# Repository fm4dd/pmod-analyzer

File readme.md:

## PMOD Analyzer

### Description

The PMOD Analyzer implements a twin-connector, pass-through PMOD board that routes 2x8 I/O signals from pinheader to pinsocket with breakout into a 18-pin 2.54mm header row for connecting protocol analyzers, and 20 test points for mini-grabber hook-ups that are useful for oscilloscope measurements. Lastly, each signal can be individually switched on to drive a control LED on each I/O line. This makes it ideal for troubleshooting by inserting it between a controller board and PMOD peripherals. With the LEDs switched on, the PMOD can operate "standalone" as a normal LED output board.

http://fpga.fm4dd.com/

### Schematic

### PCB Gerber

| Version | Gerber | Schema |
|---------|--------|--------|
| 1.0     |[20230218-pmod-analyzer-gerber.zip](fabfiles/v10/20230218-pmod-analyzer-gerber.zip) | [20230218-pmod-analyzer-schema.pdf](fabfiles/v10/20230218-pmod-analyzer-schema.pdf) |

### Board Pictures

PMOD Analyzer, connected to the Gatemate E1 FPGA board.

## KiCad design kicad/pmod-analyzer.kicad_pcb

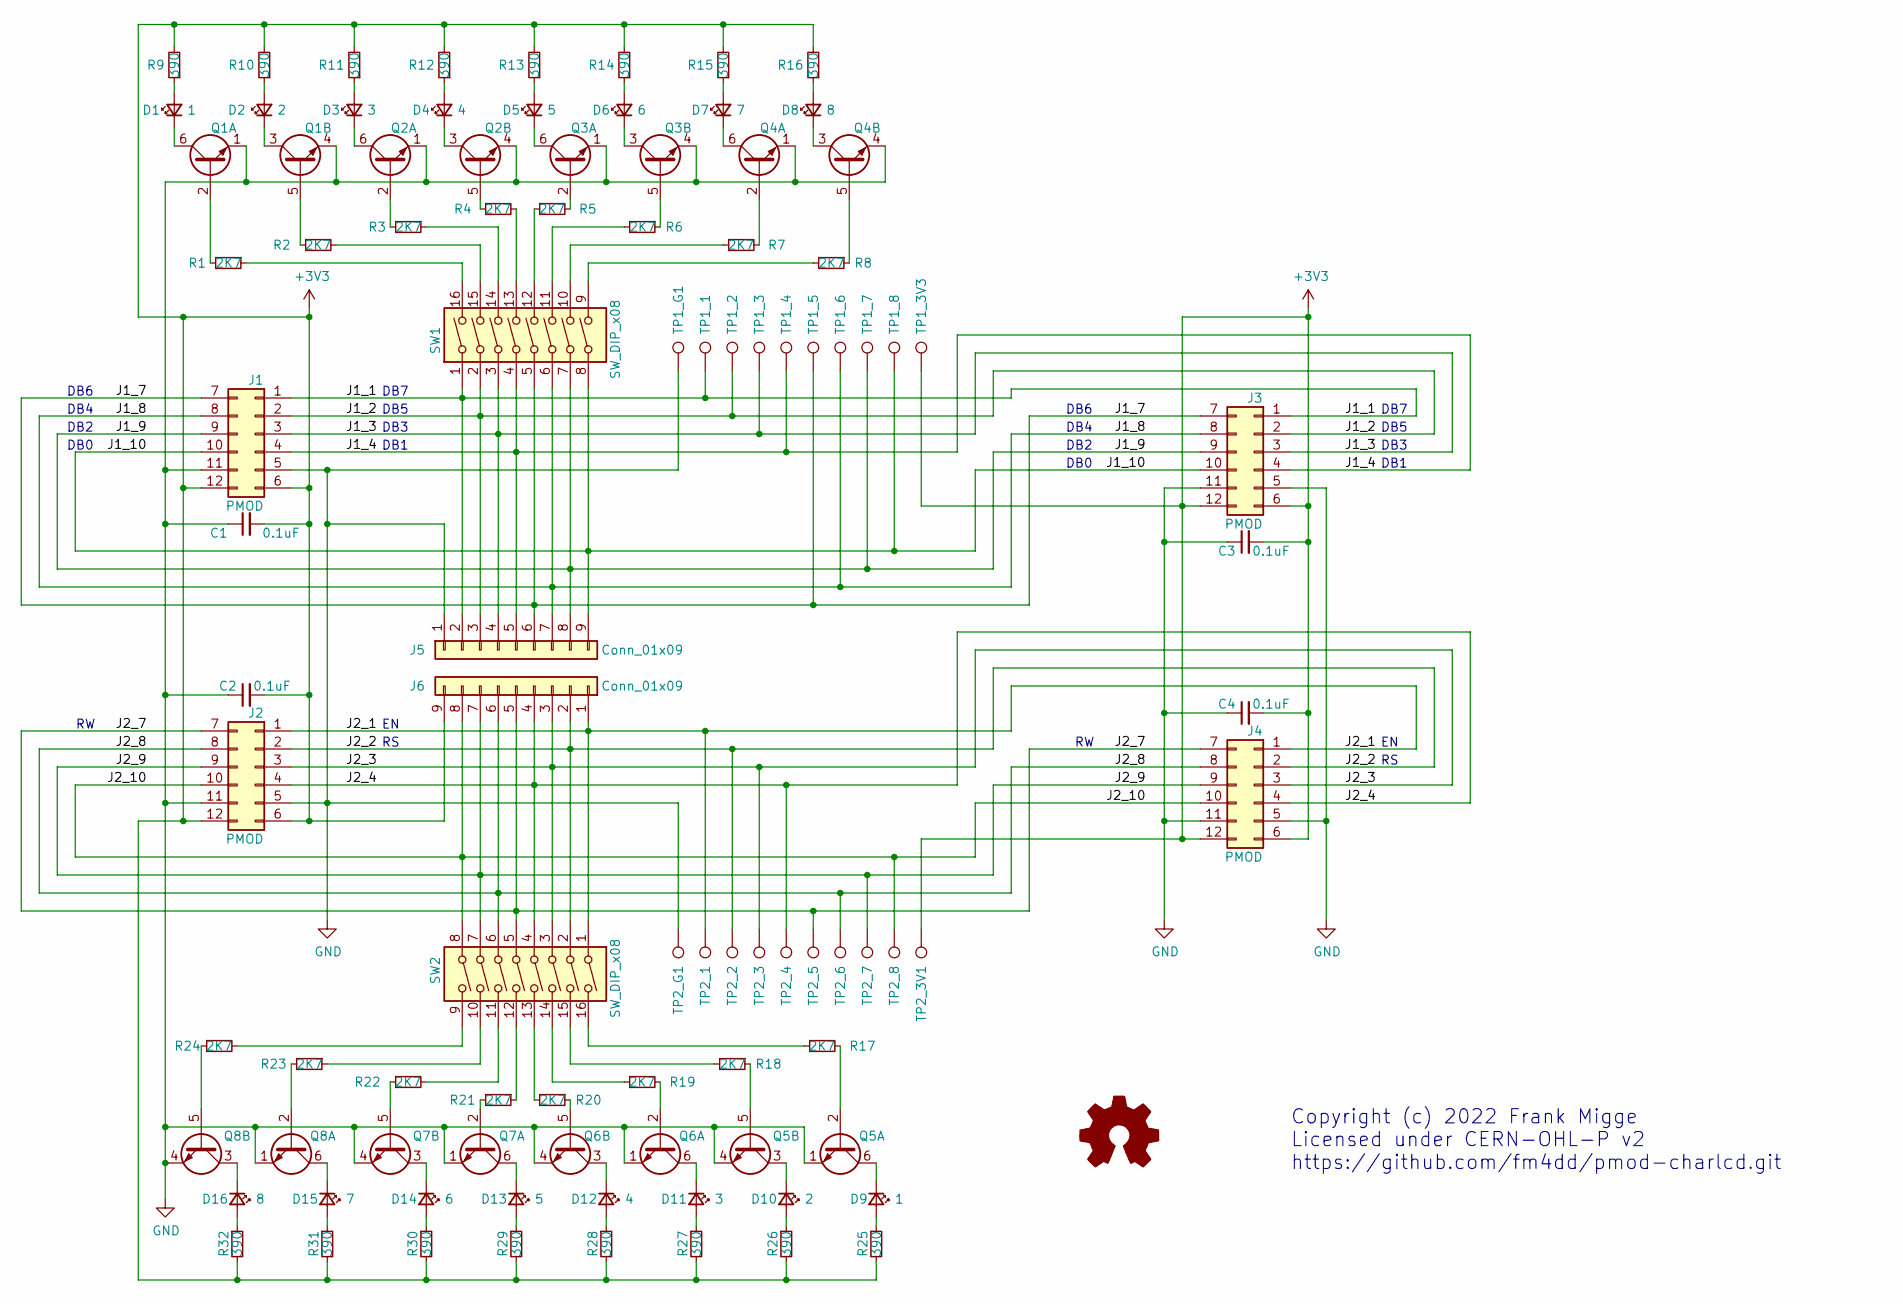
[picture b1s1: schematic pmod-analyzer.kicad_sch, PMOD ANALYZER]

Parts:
C1, C2, C3, C4: 0.1uF; C_0402_1005Metric
D1, D9: 1; LED_0402_FPGA
D2, D10: 2; LED_0402_FPGA
D3, D11: 3; LED_0402_FPGA
D4, D12: 4; LED_0402_FPGA
D5, D13: 5; LED_0402_FPGA
D6, D14: 6; LED_0402_FPGA
D7, D15: 7; LED_0402_FPGA
D8, D16: 8; LED_0402_FPGA
J1, J2: PMOD; PMODHeader_2x06_P2.54mm_Horizontal
J3, J4: PMOD; PMODPinSocket_2x06_P2.54mm_Horizontal
J5, J6: Conn_01x09; PinHeader_1x09_P2.54mm_Vertical
Q1, Q2, Q3, Q4, Q5, Q6, Q7, Q8: Q_Dual_NPN_NPN_E1B1C2E2B2C1; SOT-363_SC-70-6
R1, R2, R3, R4, R5, R6, R7, R8, R17, R18, R19, R20, R21, R22, R23, R24: 2K7; R_0402_1005Metric
R9, R10, R11, R12, R13, R14, R15, R16, R25, R26, R27, R28, R29, R30, R31, R32: 390; R_0402_1005Metric
SW1, SW2: SW_DIP_x08; SW_DIP_SPSTx08_Slide_6.7x21.88mm_W7.62mm_P2.54mm_LowProfile
TP1_1: 1_1; TestPoint_Keystone_5000-5004_Miniature
TP1_2: 1_2; TestPoint_Keystone_5000-5004_Miniature
TP1_3: 1_3; TestPoint_Keystone_5000-5004_Miniature
TP1_3V3: 1_3V; TestPoint_Keystone_5000-5004_Miniature
TP1_4: 1_4; TestPoint_Keystone_5000-5004_Miniature
TP1_5: 1_5; TestPoint_Keystone_5000-5004_Miniature
TP1_6: 1_6; TestPoint_Keystone_5000-5004_Miniature
TP1_7: 1_7; TestPoint_Keystone_5000-5004_Miniature
TP1_8: 1_8; TestPoint_Keystone_5000-5004_Miniature
TP1_G1: 1_G; TestPoint_Keystone_5000-5004_Miniature
TP2_1: 2_1; TestPoint_Keystone_5000-5004_Miniature
TP2_2: 2_2; TestPoint_Keystone_5000-5004_Miniature
TP2_3: 2_3; TestPoint_Keystone_5000-5004_Miniature
TP2_3V1: 2_3V; TestPoint_Keystone_5000-5004_Miniature
TP2_4: 2_4; TestPoint_Keystone_5000-5004_Miniature
TP2_5: 2_5; TestPoint_Keystone_5000-5004_Miniature
TP2_6: 2_6; TestPoint_Keystone_5000-5004_Miniature
TP2_7: 2_7; TestPoint_Keystone_5000-5004_Miniature
TP2_8: 2_8; TestPoint_Keystone_5000-5004_Miniature
TP2_G1: 2_G; TestPoint_Keystone_5000-5004_Miniature

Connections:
+3V3: C1.2, C2.2, C3.2, C4.2, J1.6, J1.12, J2.6, J2.12, J3.6, J3.12, J4.6, J4.12, J6.9, R9.2, R10.2, R11.2, R12.2, R13.2, R14.2, R15.2, R16.2, R25.2, R26.2, R27.2, R28.2, R29.2, R30.2, R31.2, R32.2, TP1_3V3.1, TP2_3V1.1
/J1_1: J1.1, J3.1, J5.2, SW1.1, TP1_1.1
/J1_2: J1.2, J3.2, J5.3, SW1.2, TP1_2.1
/J1_3: J1.3, J3.3, J5.4, SW1.3, TP1_3.1
/J1_4: J1.4, J3.4, J5.5, SW1.4, TP1_4.1
/J1_7: J1.7, J3.7, J5.6, SW1.5, TP1_5.1
/J1_8: J1.8, J3.8, J5.7, SW1.6, TP1_6.1
/J1_9: J1.9, J3.9, J5.8, SW1.7, TP1_7.1
/J1_10: J1.10, J3.10, J5.9, SW1.8, TP1_8.1
/J2_1: J2.1, J4.1, J6.1, SW2.1, TP2_1.1
/J2_2: J2.2, J4.2, J6.2, SW2.2, TP2_2.1
/J2_3: J2.3, J4.3, J6.3, SW2.3, TP2_3.1
/J2_4: J2.4, J4.4, J6.4, SW2.4, TP2_4.1
/J2_7: J2.7, J4.7, J6.5, SW2.5, TP2_5.1
/J2_8: J2.8, J4.8, J6.6, SW2.6, TP2_6.1
/J2_9: J2.9, J4.9, J6.7, SW2.7, TP2_7.1
/J2_10: J2.10, J4.10, J6.8, SW2.8, TP2_8.1
GND: C1.1, C2.1, C3.1, C4.1, J1.5, J1.11, J2.5, J2.11, J3.5, J3.11, J4.5, J4.11, J5.1, Q1.1 (E1), Q1.4 (E2), Q2.1 (E1), Q2.4 (E2), Q3.1 (E1), Q3.4 (E2), Q4.1 (E1), Q4.4 (E2), Q5.1 (E1), Q5.4 (E2), Q6.1 (E1), Q6.4 (E2), Q7.1 (E1), Q7.4 (E2), Q8.1 (E1), Q8.4 (E2), TP1_G1.1, TP2_G1.1
unnamed: D1.2 (A), R9.1
unnamed: D1.1 (K), Q1.6 (C1)
unnamed: D2.2 (A), R10.1
unnamed: D2.1 (K), Q1.3 (C2)
unnamed: D3.2 (A), R11.1
unnamed: D3.1 (K), Q2.6 (C1)
unnamed: D4.2 (A), R12.1
unnamed: D4.1 (K), Q2.3 (C2)
unnamed: D5.2 (A), R13.1
unnamed: D5.1 (K), Q3.6 (C1)
unnamed: D6.2 (A), R14.1
unnamed: D6.1 (K), Q3.3 (C2)
unnamed: D7.2 (A), R15.1
unnamed: D7.1 (K), Q4.6 (C1)
unnamed: D8.2 (A), R16.1
unnamed: D8.1 (K), Q4.3 (C2)
unnamed: D9.2 (A), R25.1
unnamed: D9.1 (K), Q5.6 (C1)
unnamed: D10.2 (A), R26.1
unnamed: D10.1 (K), Q5.3 (C2)
unnamed: D11.2 (A), R27.1
unnamed: D11.1 (K), Q6.6 (C1)
unnamed: D12.2 (A), R28.1
unnamed: D12.1 (K), Q6.3 (C2)
unnamed: D13.2 (A), R29.1
unnamed: D13.1 (K), Q7.6 (C1)
unnamed: D14.2 (A), R30.1
unnamed: D14.1 (K), Q7.3 (C2)
unnamed: D15.2 (A), R31.1
unnamed: D15.1 (K), Q8.6 (C1)
unnamed: D16.2 (A), R32.1
unnamed: D16.1 (K), Q8.3 (C2)
unnamed: Q1.2 (B1), R1.2
unnamed: Q1.5 (B2), R2.1
unnamed: Q2.2 (B1), R3.2
unnamed: Q2.5 (B2), R4.1
unnamed: Q3.2 (B1), R5.2
unnamed: Q3.5 (B2), R6.1
unnamed: Q4.2 (B1), R7.2
unnamed: Q4.5 (B2), R8.1
unnamed: Q5.2 (B1), R17.2
unnamed: Q5.5 (B2), R18.1
unnamed: Q6.2 (B1), R19.2
unnamed: Q6.5 (B2), R20.1
unnamed: Q7.2 (B1), R21.2
unnamed: Q7.5 (B2), R22.1
unnamed: Q8.2 (B1), R23.2
unnamed: Q8.5 (B2), R24.1
unnamed: R1.1, SW1.16
unnamed: R2.2, SW1.15
unnamed: R3.1, SW1.14
unnamed: R4.2, SW1.13
unnamed: R5.1, SW1.12
unnamed: R6.2, SW1.11
unnamed: R7.1, SW1.10
unnamed: R8.2, SW1.9
unnamed: R17.1, SW2.16
unnamed: R18.2, SW2.15
unnamed: R19.1, SW2.14
unnamed: R20.2, SW2.13
unnamed: R21.1, SW2.12
unnamed: R22.2, SW2.11
unnamed: R23.1, SW2.10
unnamed: R24.2, SW2.9

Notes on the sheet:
DB0
DB1
DB2
DB4
DB7
Copyright (c) 2022 Frank Migge Licensed under CERN-OHL-P v2 https://github.com/fm4dd/pmod-charlcd.git
DB6
DB3
DB5

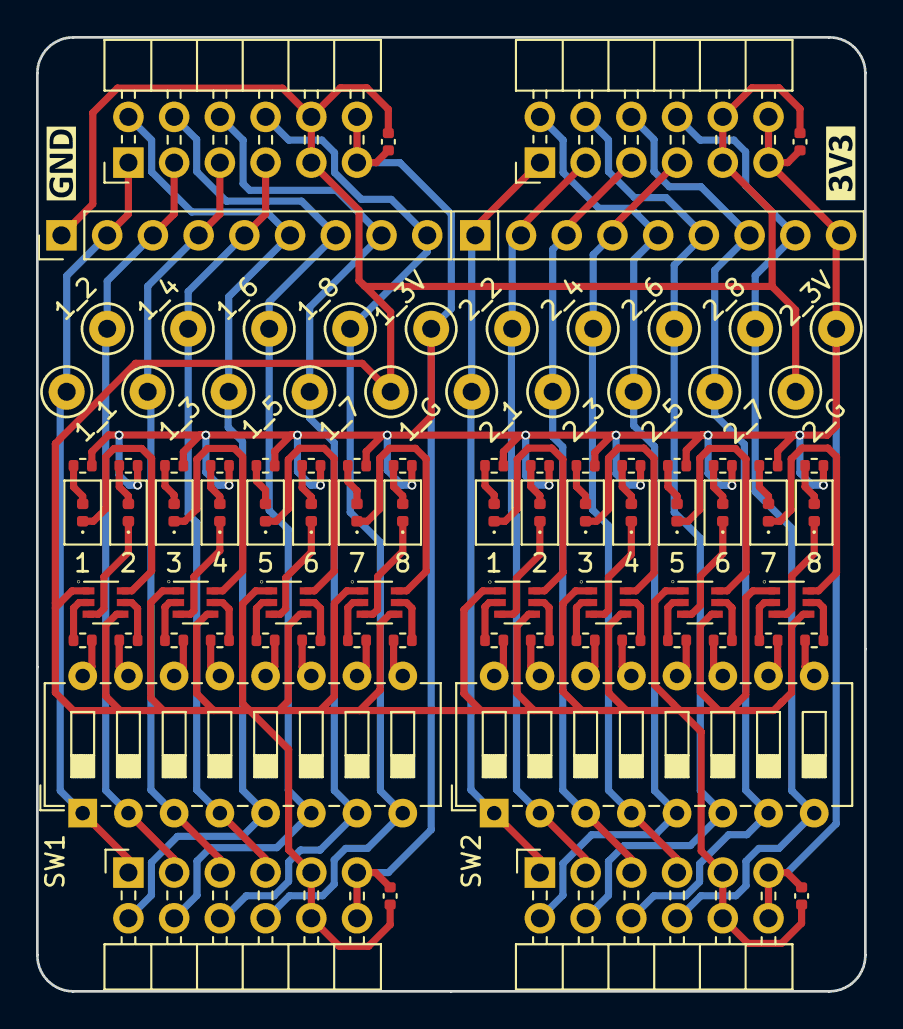
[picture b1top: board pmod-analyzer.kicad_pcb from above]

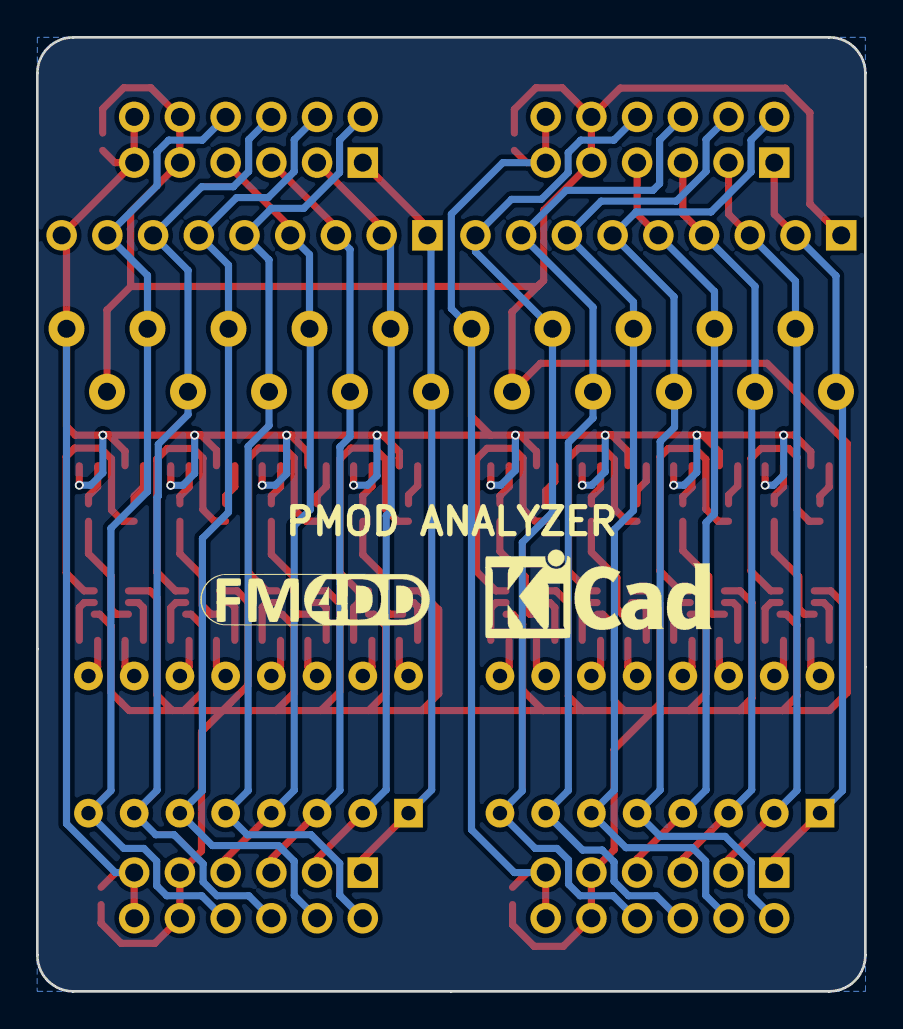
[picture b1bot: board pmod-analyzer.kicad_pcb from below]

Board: 2 copper layers, 46.0 x 53.0 mm, 90 parts (2 on the bottom side), 82 nets.

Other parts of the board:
Ref**: 1; Logo_FM4DD_5mm_SScr
Ref**#2: Logo_KiCad_5mm_SScr

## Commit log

2023-08-23 initial check-in
2023-09-06 add device SVG for documentations

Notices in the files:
kicad/pmod-analyzer.kicad_pcb:
License: CC-BY-SA 4.0
